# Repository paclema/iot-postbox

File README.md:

# IoT-PostBox

IoT-PostBox is a complete smart mailbox sensor solution that monitors mailbox activity and sends wireless notifications when events occur. The project consists of custom hardware designs with integrated battery management and charging system, and firmware that monitors switch sensors to detect mailbox events. The hardware has evolved from initial ESP8266-based designs (IoT-PostBox v0.x) to current ESP32S2-based designs (IoT-PostBox v1.x) with added LoRaWAN capabilities for extended range communication beyond WiFi and a optimized power management system. The device is designed for battery-powered operation with onboard charging circuitry. When an event is detected, the device wakes from deep sleep, connects wirelessly (WiFi or LoRa), publishes the event via MQTT or LoRaWAN, and returns to sleep to maximize battery life. The system includes device configuration and management through the WebConfigServer library, which provides a web-based dashboard to visualize data and handle device configurations easily using a config.json file.

**Installation and use:** The device is installed inside the mailbox with switches positioned to detect when the mail slot or door is opened. One switch can detect mail insertion (when the slot is opened to insert mail), while another can detect mail collection (when the mailbox door is opened to retrieve mail). This allows monitoring both mail delivery and pickup events.

**Hardware evolution:**
- **v0.x (ESP8266):** WiFi-only communication, basic power management using CH_PD pin to disable the microcontroller, battery charging system, switch sensor inputs.
- **v1.x (ESP32-S2):** Enhanced with LoRaWAN capability, improved power management with deep sleep modes managed by interrupts (allowing identification of wake-up source via WAKE_UP_BITMASK), advanced battery management, native USB programming, and expanded I/O options.

> [!NOTE]  
> For detailed hardware specifications, BOMs, and pinouts, see [`pcb_desings/readme.md`](pcb_desings/).

---

## 📁 Repository Structure

- `/src/` — Main firmware source code for IoT-PostBox
- `/pcb_desings/` — Hardware designs, documentation, BOMs, gerbers, and 3D models
- `/data/` — SPIFFS filesystem data (configs, static webapp, certificates)
- `/platformio.ini` — PlatformIO project configuration

---

## ⚡ Getting Started

1. **Select and configure your hardware:** 
   - **For IoT-PostBox PCBs:** Choose between IoT-PostBox v0.x (ESP8266-based) or IoT-PostBox v1.x (ESP32-S2-based) versions. See [`pcb_desings/readme.md`](pcb_desings/readme.md) for detailed specifications.
   - **For development boards:** The firmware also supports various ESP8266/ESP32 development boards (see available targets in `platformio.ini`), but full compatibility and functionality is only guaranteed with the custom IoT-PostBox PCBs designed for this purpose.
   - Configure the appropriate target in `platformio.ini` for your hardware version (e.g., `IoT-PostBox_v1` for IoT-PostBox v1.x PCB).
   - Edit `data/config/config.json` with your initial configuration (WiFi credentials, MQTT settings, etc.) following the WebConfigServer library standard.

2. **Upload SPIFFS data:**
   ```sh
   pio run -t uploadfs
   ```

3. **Build and upload firmware:** Use PlatformIO to compile and flash the firmware to your device.

4. **Configure the device:** Access the web dashboard hosted by the device for WiFi, MQTT, and power management setup, or update the configuration by editing `config.json` and re-uploading SPIFFS data.

---

## 📈 Web Dashboard

The static web dashboard is provided by the [WebConfigServer](https://github.com/paclema/WebConfigServer) library and served directly from the device.

If you need to customize the dashboard:
- Go to the WebConfigServer repository and follow the build instructions
- Copy the generated static files to the `/data/` folder
- Upload `/data/` to the device SPIFFS

---

## 📚 Dependencies

This project uses the following main libraries:
- [WebConfigServer](https://github.com/paclema/WebConfigServer) - Web dashboard and device configuration management
- [PowerManagement](https://github.com/paclema/PowerManagement) - Battery monitoring and power management

---

## 📄 License

[![CC BY-NC-SA 4.0][cc-by-nc-sa-image]][cc-by-nc-sa]&nbsp;&nbsp;&nbsp;<a property="dct:title" rel="cc:attributionURL" href="https://github.com/paclema/iot-postbox"> IoT-PostBox</a> © 2019-2025 by <a rel="cc:attributionURL dct:creator" property="cc:attributionName" href="http://www.paclema.com/">paclema</a> is licensed under <a href="http://creativecommons.org/licenses/by-nc-sa/4.0/?ref=chooser-v1" target="_blank" rel="license noopener noreferrer" style="display:inline-block;">CC BY-NC-SA 4.0</a>

**Hardware and firmware designs** are provided for educational and non-commercial use. For commercial use, please contact the author for permission.

[cc-by-nc-sa]: http://creativecommons.org/licenses/by-nc-sa/4.0/
[cc-by-nc-sa-image]: https://licensebuttons.net/l/by-nc-sa/4.0/88x31.png

---

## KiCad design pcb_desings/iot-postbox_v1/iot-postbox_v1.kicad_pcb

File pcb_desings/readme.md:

# IoT-PostBox PCB Designs

This folder contains all hardware designs for the IoT-PostBox project. These PCBs are intended for ultra-low power event detection and wireless notification, ideal for smart mailboxes or similar battery-powered IoT applications. The boards are designed to maximize battery life by staying in deep sleep and only waking up when an event is detected.  
**Typical use case:** Mount a switch at the mailbox slot or door to detect when a letter or package is inserted, triggering a wireless notification.

---

## 📝 How It Works

- **Event Detection:** The boards monitor switches (J1/J2) for events such as mailbox opening or mail insertion.
- **Wake-Up:** ESP8266 boards power on from switches, ESP32-S2 boards wake from deep sleep via GPIO interrupts
- **Notification:** Events are sent wirelessly (WiFi/MQTT for ESP8266, WiFi/MQTT and LoRaWAN for ESP32-S2)
- **Power Management:** Battery charging and monitoring circuits ensure safe operation and long battery life.

---

## 📦 IoT-Postbox v0.X (ESP8266/ESP-12)

- **Folder:** [`iot-postbox/`](iot-postbox/)
- **MCU:** ESP8266 (ESP-12F or ESP-07S)
- **Wake-up:** When either switch input (J1 or J2) closes, it physically pulls the CH_PD pin high, powering on the ESP8266 from a completely powered-down state. Once powered on, the firmware immediately activates GPIO14 to maintain CH_PD high, ensuring the system stays powered even if the switch opens during the notification process. After completing the notification and a configured delay, GPIO14 goes low, completely powering down the ESP8266 for maximum battery savings. The board can also be configured for deep sleep mode or continuous operation instead of complete power down via the onboard web app.
- **Features:**
  - Battery charger (TP4056) with overcharge, overdischarge, and overcurrent protection
  - Power management with LDO (candidates: ME6211 or MCP1700)
  - Switch sensor inputs for mailbox event detection
  - Deep sleep and wake-up logic via GPIO
  - WiFi and MQTT notifications for remote monitoring
- **Versions:**
  | v0.0 | v0.3 |
  |:----:|:----:|
  |  |  |
  | *First version* <br> Basic mailbox sensor with battery charger and power management. | *Added WS2812B LED strip for notifications* <br> *Updated battery sense resistors for improved ADC accuracy* <br> *Changed switch pinouts for better integration* |

- **Programming & Debugging:**  
  For ESP8266-based boards, external programming is required. Two options available:
  
  **Option 1: TTL-to-USB Adapter + FTDI Breakout**
  | Top View | Bottom View |
  |:------------------:|:----------------:|
  |  |  |
  - **Repository:** [`ttl_to_usb_adapter/`](ttl_to_usb_adapter/)
  - Converts DTR/RTS signals from an USB to Serial FTDI breakout board to ESP8266 boot sequence
  - Dedicated jumper for CH_PD control during programming

  **Option 2: Integrated USB Bridge**
  - **USBtoUART:** Complete solution available at [paclema.com/projects/usbtouart/](https://paclema.com/projects/usbtouart/) or at github.com/paclema/USBtoUART
  - Single device with integrated USB-to-UART conversion

---

## 📦 IoT-Postbox v1 (ESP32-S2)

- **Folder:** [`iot-postbox_v1/`](iot-postbox_v1/)
- **MCU:** ESP32-S2
- **Wake-up:** Switches (J1/J2) are configured as GPIO interrupts to wake up the MCU from deep sleep, instead of physically powering on the board (as in ESP8266). This allows more flexible event handling and enables distinguishing between different events.
- **Features:**
  - LoRa support (RFM95W module footprints)
  - Up to 16MB flash and 8MB PSRAM (optional, depending on SoC version)
  - Improved battery and power management (dedicated ADC sense for VBAT and VBUS)
  - Modular schematic split into INTERFACE, MCU, and POWER sections
  - Selectable onboard/uFL antennas for WiFi (JP1) and LoRa (JP2) by populating the correct resistor
  - Dedicated JTAG debug port
  - Multiple jumpers and test points on the back for configuration and debugging (including RPROG selection for battery charger IC)

- **Latest version:** IoT-PostBox v1.2
  | Top View | Bottom View |
  |:--------------:|:----------------:|
  |  |  |

- **Programming & Debugging:**  
  Programming and debugging for the ESP32-S2 board does **not require an external USB-to-UART bridge**. The ESP32-S2 features a native USB interface (USB-CDC/JTAG), allowing direct programming and serial communication via the onboard USB connector. Simply connect the board to your computer using a USB cable for firmware flashing and debugging.

### LiPo Charger & RPROG Selection

The onboard charger circuit is designed to be compatible with MCP73831/2, TP4054, and TP4065 ICs, allowing any of these to be used. The charging current is set by the RPROG resistor.

- **For MCP73831/2 (max 500mA) and TP4054 (max 800mA):**
  ```
  Ichg (mA) = 1000(v) / R(kΩ)
  ```
  | RPROG (Ω) | Charging Current (mA) |
  |-----------|----------------------|
  | 10k       | 100                  |
  | 5k        | 200                  |
  | 2k2       | 455                  |
  | 2k        | 500                  |
  | 1k        | 1000                 |

- **For TP4065 (max 600mA):**
  ```
  Ichg (mA) = 1100(v) / R(kΩ)
  ```
  | RPROG (Ω) | Charging Current (mA) |
  |-----------|----------------------|
  | 2k2       | 500                  |
  | 2k        | 600                  |

- **Note:**  
  - Choose the RPROG value based on your battery's specifications and desired charging speed.
  - Protections: Battery and input reverse polarity protection but no temperature or overcurrent protection.

- **VBAT_STAT output:**  
  - Tri-state output: for MCP73831.
  - Open-drain output: for MCP7383, TP4054 and TP4065.
  - Only for open-drain, `R18` makes sense because VDD_STAT can be configurable only in that case.
  - Monitored using ESP32-S2 GPIO3/ADC1_CH2 pin.

### Pinout Reference (IoT-Postbox v1.2)

Below are the pinouts for the main connectors on the back of the IoT-Postbox v1.2 PCB, including signal and ESP32-S2 functions:

#### J6 (EXT1 Expansion Port):

| Pin | Signal   | Function                                            |
|-----|----------|--------------------------------------------------------|
| 1   | GPIO46   | Strapping pin (can be used for boot mode selection)    |
| 2   | GPIO45   | Strapping pin (can be used for VDD_SPI selection)      |
| 3   | GPIO44   | UART0 RXD (default)                                    |
| 4   | GPIO43   | UART0 TXD (default)                                    |
| 5   | GPIO38   | I2C SCL (default)                                      |
| 6   | GPIO37   | SPI MISO (default)                                     |

#### J3 (LED Port):

| Pin | Signal      | Function                                 |
|-----|-------------|---------------------------------------------|
| 1   | VCC         | Power for LED strip (3V3_LDO2)              |
| 2   | RGB_LED_PWM | PWM output for RGB LED strip                |
| 3   | GND         | Ground                                      |

#### J5 (Power Output Port):

| Pin | Signal   | Function                                   |
|-----|----------|-----------------------------------------------|
| 1   | 3V3_LDO2 | Power output from peripheral LDO              |
| 2   | GND      | Ground                                        |

#### SW1 (Switch Sensor 1):

| Pin | Signal   | Function                                   |
|-----|----------|-----------------------------------------------|
| 1   | 3V3_LDO  | Power for switch sensor                       |
| 2   | SW1      | Digital input (event detection, GPIO input)   |

#### SW2 (Switch Sensor 2):

| Pin | Signal   | Function                                   |
|-----|----------|-----------------------------------------------|
| 1   | 3V3_LDO  | Power for switch sensor                       |
| 2   | SW2      | Digital input (event detection, GPIO input)   |

#### J7 (EXT2 Expansion Port):

| Pin | Signal   | Function                                   |
|-----|----------|-----------------------------------------------|
| 1   | CHIP_PU  | ESP32-S2 enable (power up, active high)       |
| 2   | BOOT     | Boot mode selection (GPIO0, strapping pin)    |
| 3   | GPIO34   | SPI MOSI (default)                            |
| 4   | GPIO35   | SPI SCK (default)                             |
| 5   | GPIO36   | SPI CS (default)                              |
| 6   | GPIO33   | I2C SDA (default)                             |

---

### 📚 Libraries

- **Folder:** [`libs/`](libs/)
- Contains KiCad symbols, footprints and 3D models, including Espressif official libraries and miscellaneous modules.

---

### 🛠️ Submodules Installation for KiCad

To pull KiCad lib submodules, run:
```sh
git submodule update --init --recursive
```

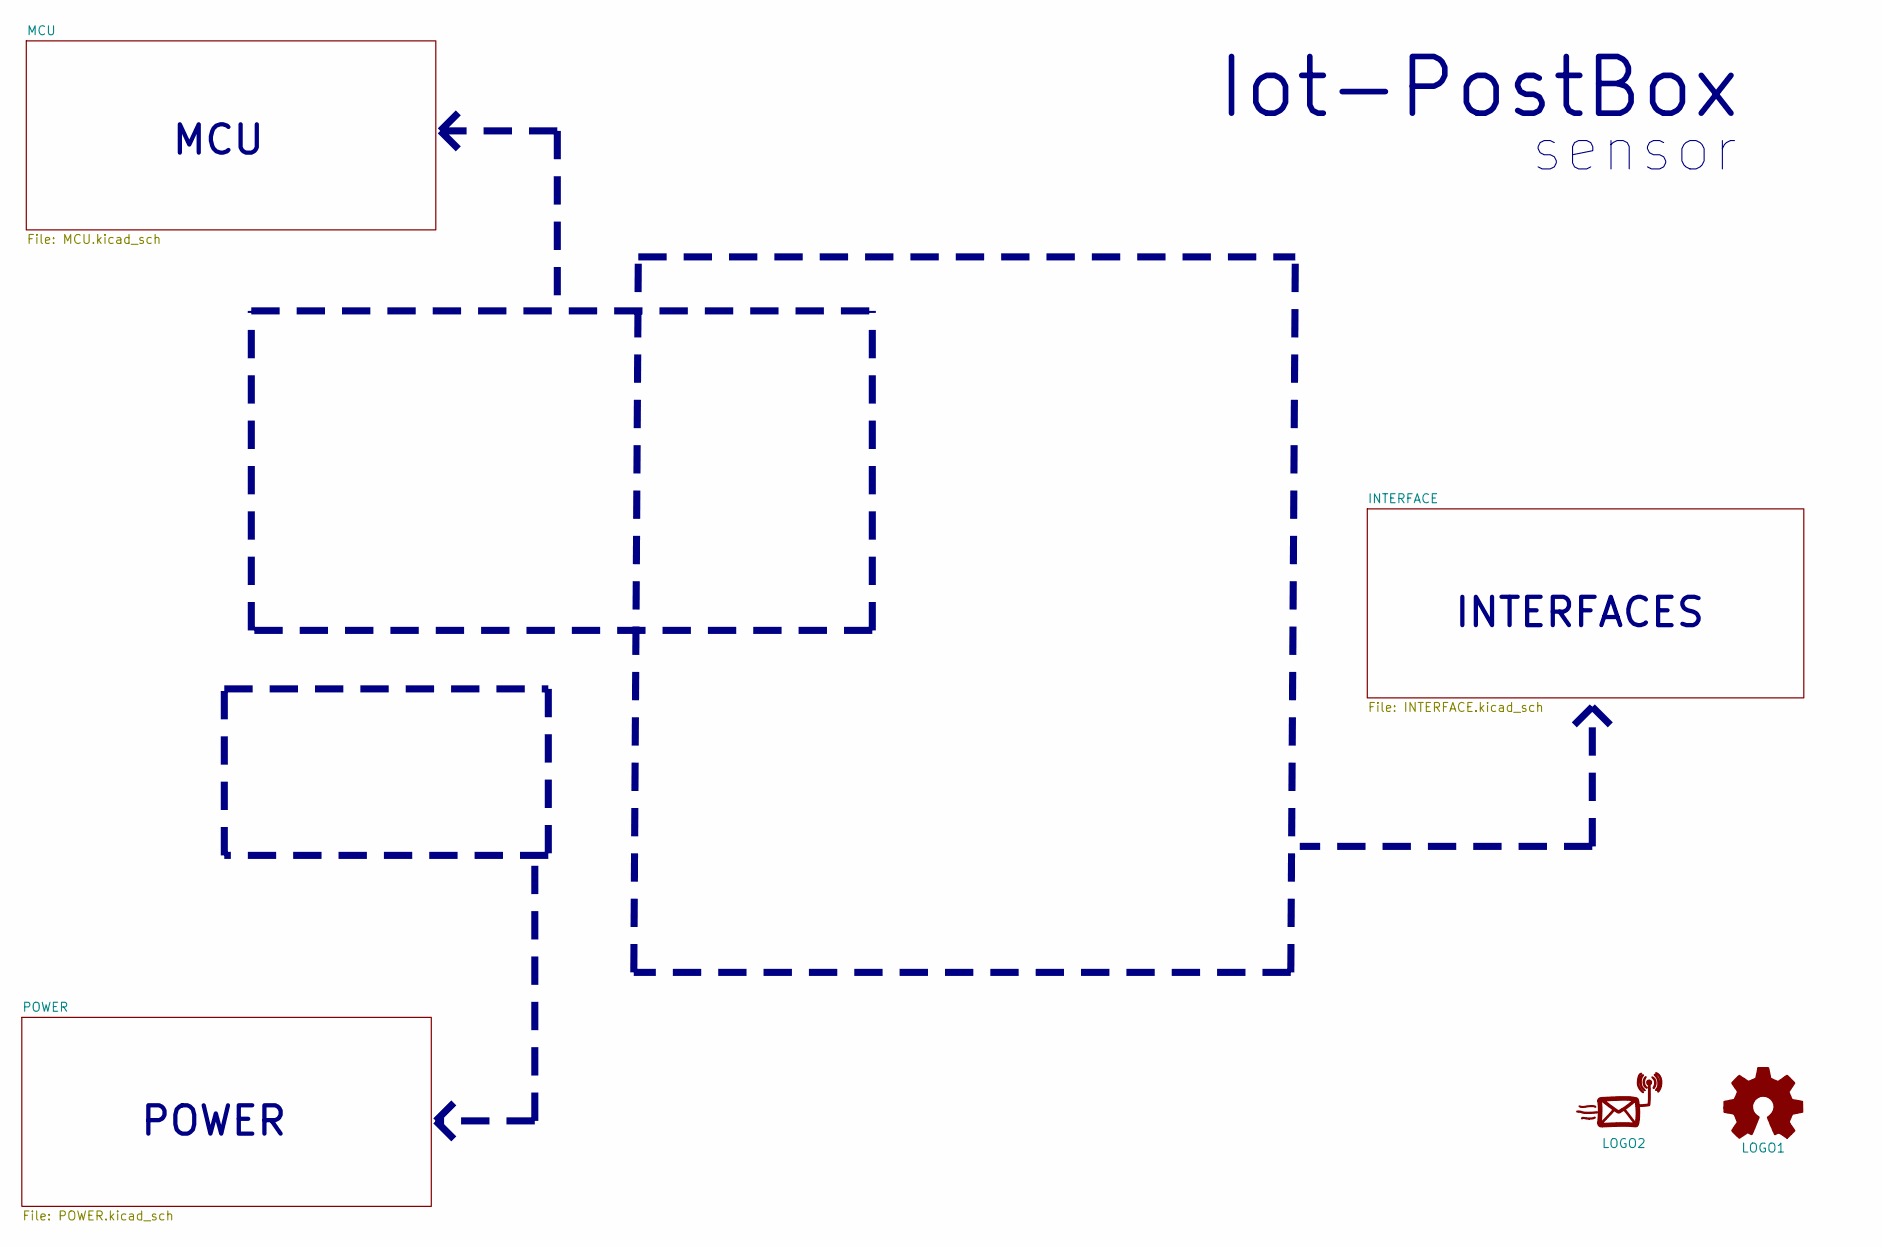
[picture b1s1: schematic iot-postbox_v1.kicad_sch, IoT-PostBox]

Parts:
LOGO1: Logo_Open_Hardware_Small; OSHW-Logo_5.7x6mm_SilkScreen
LOGO2: iot-postbox_logo

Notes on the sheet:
Iot-PostBox
POWER
INTERFACES
MCU
sensor

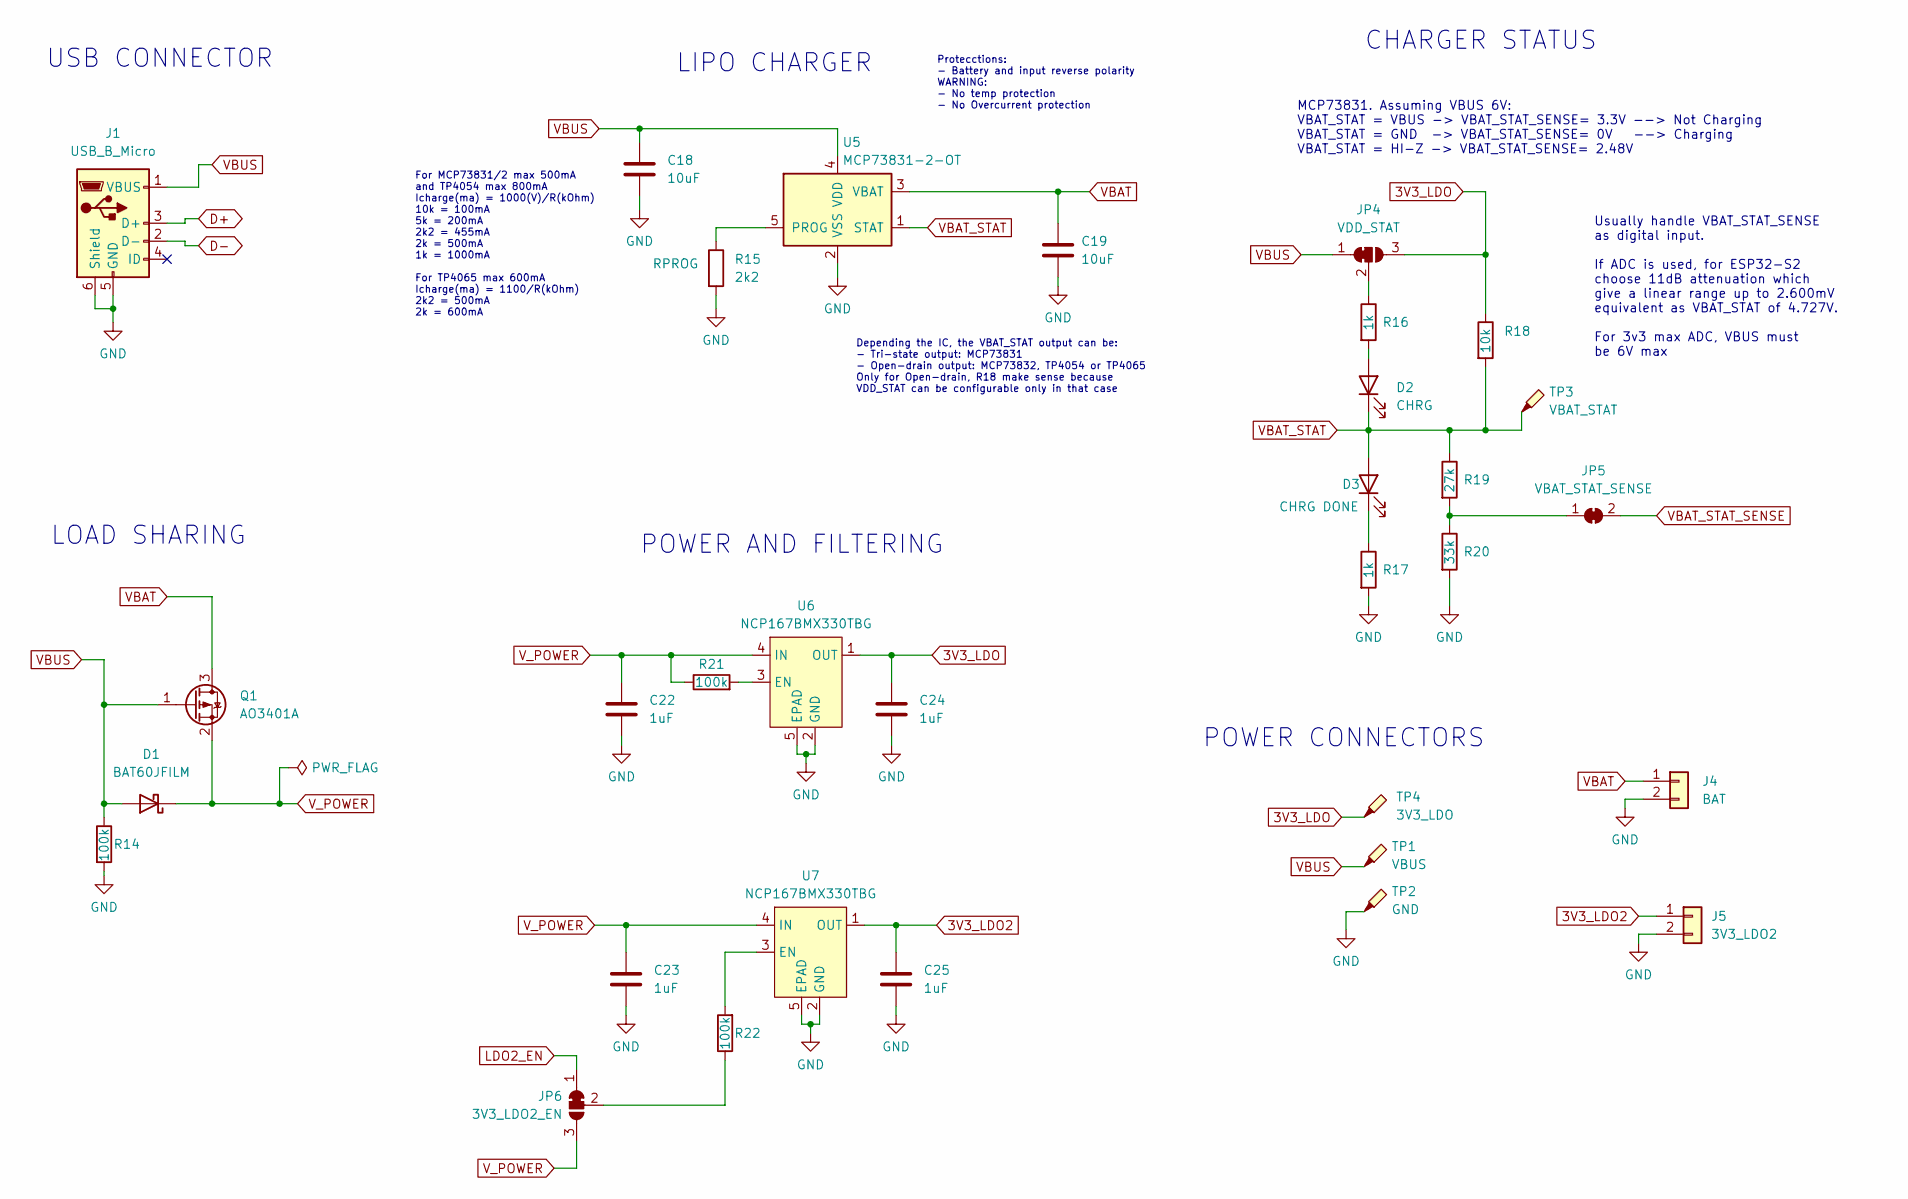
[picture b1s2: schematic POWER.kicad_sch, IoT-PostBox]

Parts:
C18, C19: 10uF; C_1206_3216Metric; Mouser CL31A106KAHNNNF
C22, C23, C24, C25: 1uF; C_0603_1608Metric; Mouser CL10A105KA8NNNC
D1: BAT60JFILM; D_SOD-323; LCSC C133103
D2: CHRG; LED_0805_2012Metric
D3: CHRG DONE; LED_0805_2012Metric
J1: USB_B_Micro; USB_Micro-B_Amphenol_10118194_Horizontal
J4: BAT; PinHeader_1x02_P2.54mm_Vertical
J5: 3V3_LDO2; PinHeader_1x02_P2.54mm_Vertical
JP4: VDD_STAT; SolderJumper-3_P1.3mm_Bridged12_RoundedPad1.0x1.5mm_NumberL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
JP5: VBAT_STAT_SENSE; SolderJumper-2_P1.3mm_Bridged_RoundedPad1.0x1.5mm
JP6: 3V3_LDO2_EN; SolderJumper-3_P1.3mm_Bridged12_RoundedPad1.0x1.5mm_NumberL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
Q1: AO3401A; SOT-23; LCSC C2836398
R14: 100k; R_0805_2012Metric; Mouser RC0805FR-07100KL
R15: 2k2; R_0805_2012Metric; Mouser CR0805-JW-222ELF
R16, R17: 1k; R_0805_2012Metric; Mouser AC0805FR-071KL
R18: 10k; R_0805_2012Metric; Mouser AC0805JR-0710KL
R19: 27k; R_0805_2012Metric; Mouser RC0805FR-1327KL
R20: 33k; R_0805_2012Metric; Mouser RC0805FR-0733KL
R21, R22: 100k; R_0603_1608Metric; Mouser RK73B1JTTD104J
TP1: VBUS; TestPoint_Pad_D2.5mm
TP2: GND; TestPoint_Pad_D2.5mm
TP3: VBAT_STAT; TestPoint_Pad_D2.0mm
TP4: 3V3_LDO; TestPoint_Pad_D2.0mm
U5: MCP73831-2-OT; SOT-23-5; Mouser MCP73831T-2ACI/OT
U6, U7: NCP167BMX330TBG; NCP167BMX330TBG_XDFN4; Mouser NCP167BMX330TBG

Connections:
3V3_LDO: C24.1, JP4.3 (B), R18.1, TP4.1, U6.1 (OUT); also elsewhere on the board
3V3_LDO2: C25.1, J5.1, U7.1 (OUT); also elsewhere on the board
D+: J1.3 (D+); also elsewhere on the board
D-: J1.2 (D-); also elsewhere on the board
GND: C18.2, C19.2, C22.2, C23.2, C24.2, C25.2, J1.5 (GND), J1.6 (Shield), J4.2, J5.2, R14.2, R15.2, R17.2, R20.2, TP2.1, U5.2 (VSS), U6.2 (GND), U6.5 (EPAD), U7.2 (GND), U7.5 (EPAD); also elsewhere on the board
LDO2_EN: JP6.1 (A); also elsewhere on the board
unnamed: D2.2 (A), R16.2
unnamed: D3.1 (K), R17.1
unnamed: JP4.2 (C), R16.1
unnamed: JP5.1 (A), R19.2, R20.1
unnamed: JP6.2 (C), R22.1
unnamed: R15.1, U5.5 (PROG)
unnamed: R21.2, U6.3 (EN)
unnamed: R22.2, U7.3 (EN)
VBAT: C19.1, J4.1, Q1.3 (D), U5.3 (VBAT); also elsewhere on the board
VBAT_STAT: D2.1 (K), D3.2 (A), R18.2, R19.1, TP3.1, U5.1 (STAT)
VBAT_STAT_SENSE: JP5.2 (B); also elsewhere on the board
VBUS: C18.1, D1.2 (A), J1.1 (VBUS), JP4.1 (A), Q1.1 (G), R14.1, TP1.1, U5.4 (VDD); also elsewhere on the board
V_POWER: C22.1, C23.1, D1.1 (K), JP6.3 (B), Q1.2 (S), R21.1, U6.4 (IN), U7.4 (IN); also elsewhere on the board

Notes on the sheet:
LOAD SHARING
POWER CONNECTORS
Usually handle VBAT_STAT_SENSE as digital input. If ADC is used, for ESP32-S2 choose 11dB attenuation which give a linear range up to 2.600mV equivalent as VBAT_STAT of 4.727V. For 3v3 max ADC, VBUS must be 6V max
For MCP73831/2 max 500mA and TP4054 max 800mA Icharge(ma) = 1000(V)/R(kOhm) 10k = 100mA 5k = 200mA 2k2 = 455mA 2k = 500mA 1k = 1000mA For TP4065 max 600mA Icharge(ma) = 1100/R(kOhm) 2k2 = 500mA 2k = 600mA
POWER AND FILTERING
CHARGER STATUS
Depending the IC, the VBAT_STAT output can be: - Tri-state output: MCP73831 - Open-drain output: MCP73832, TP4054 or TP4065 Only for Open-drain, R18 make sense because VDD_STAT can be configurable only in that case
LIPO CHARGER
Protecctions: - Battery and input reverse polarity WARNING: - No temp protection - No Overcurrent protection
MCP73831. Assuming VBUS 6V: VBAT_STAT = VBUS -> VBAT_STAT_SENSE= 3.3V --> Not Charging VBAT_STAT = GND -> VBAT_STAT_SENSE= 0V --> Charging VBAT_STAT = HI-Z -> VBAT_STAT_SENSE= 2.48V
USB CONNECTOR

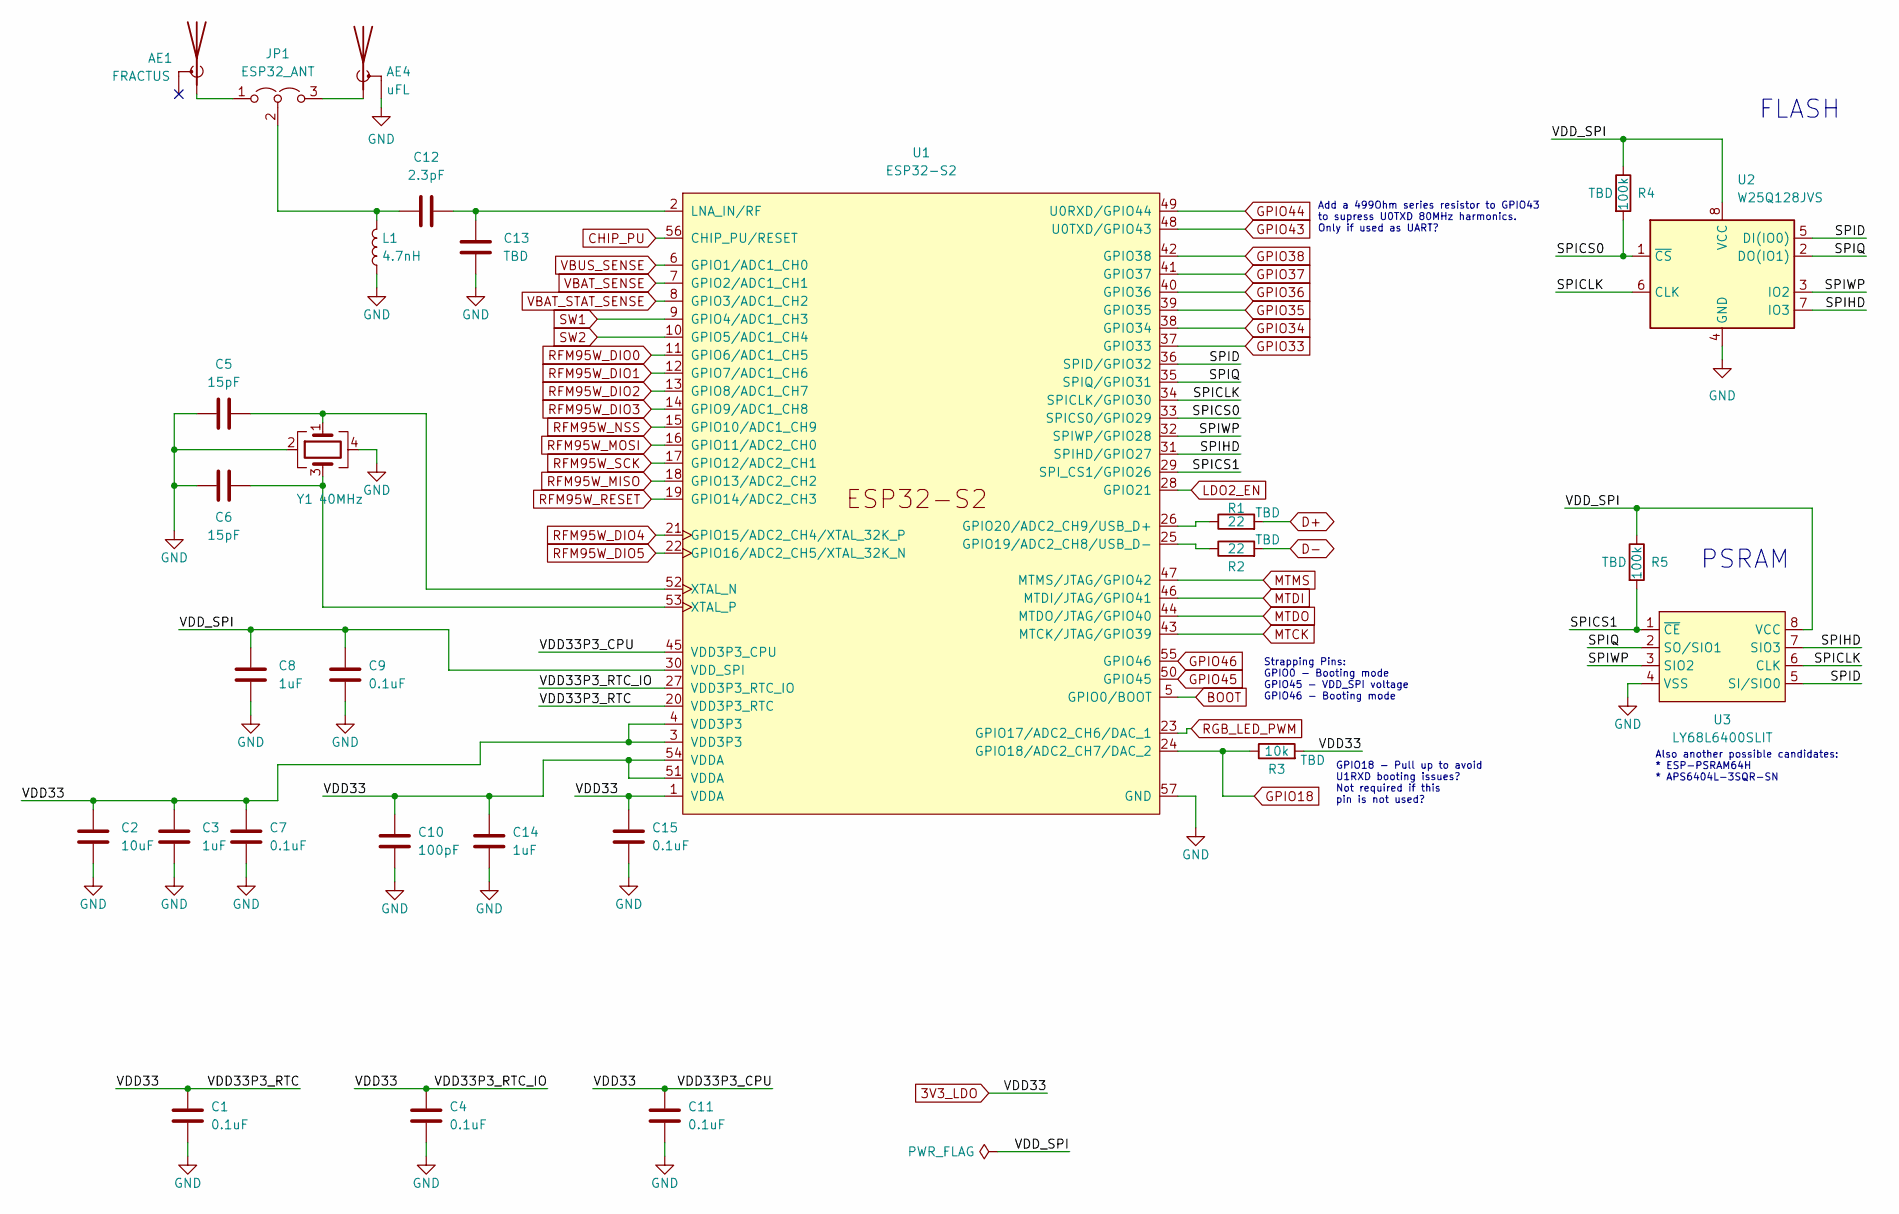
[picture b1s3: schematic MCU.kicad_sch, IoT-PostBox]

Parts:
AE1: FRACTUS; NN01-102; Mouser NN01-102
AE4: uFL; U.FL_Molex_MCRF_73412-0110_Vertical; Mouser RECE.20279.001E.01
C1, C4, C7, C9, C11, C15: 0.1uF; C_0603_1608Metric; Mouser CL10B104KB8NNWC
C2: 10uF; C_1206_3216Metric; Mouser CL31A106KAHNNNF
C3, C8, C14: 1uF; C_0805_2012Metric; Mouser EMK212BJ105KG-T
C5, C6: 15pF; C_0603_1608Metric; Mouser 06035A150JAT2A
C10: 100pF; C_0603_1608Metric; Mouser GRM1885C1H101JA01D
C12: 2.3pF; C_0402_1005Metric; Mouser GRM1555C2A2R3CA01J
C13: TBD; C_0402_1005Metric; Mouser AC0402JR-130RL
JP1: ESP32_ANT; Jumper_0402_x3; Mouser AC0402JR-130RL
L1: 4.7nH; L_0402_1005Metric; Mouser LCCI0402S4N7GTAR or shielded 7447840047G
R1, R2: 22; R_0603_1608Metric; Mouser RC0603FR-1022RL
R3: 10k; R_0603_1608Metric; Mouser RC0603JR-0710KL
R4, R5: 100k; R_0603_1608Metric; Mouser RK73B1JTTD104J
U1: ESP32-S2; ESP32_S2_QFN56; Mouser ESP32-S2
U2: W25Q128JVS; SOIC-8_5.23x5.23mm_P1.27mm; Mouser W25Q128JVSIM TR
U3: LY68L6400SLIT; SOP-8_3.9x4.9mm_P1.27mm; LCSC C261881
Y1: 40MHz; ECS-400-10-37B2-CKM-TR; Mouser ECS-400-10-37B2-CKM

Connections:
3V3_LDO: C1.1, C2.1, C3.1, C4.1, C7.1, C10.1, C11.1, C14.1, C15.1, R3.2, U1.1 (VDDA), U1.3 (VDD3P3), U1.4 (VDD3P3), U1.20 (VDD3P3_RTC), U1.27 (VDD3P3_RTC_IO), U1.45 (VDD3P3_CPU), U1.51 (VDDA), U1.54 (VDDA); also elsewhere on the board
/MCU/SPICLK: U1.34 (SPICLK/GPIO30), U2.6 (CLK), U3.6 (CLK)
/MCU/SPICS0: R4.2, U1.33 (SPICS0/GPIO29), U2.1 (~CS)
/MCU/SPICS1: R5.2, U1.29 (SPI_CS1/GPIO26), U3.1 (~CE)
/MCU/SPID: U1.36 (SPID/GPIO32), U2.5 (DI(IO0)), U3.5 (SI/SIO0)
/MCU/SPIHD: U1.31 (SPIHD/GPIO27), U2.7 (IO3), U3.7 (SIO3)
/MCU/SPIQ: U1.35 (SPIQ/GPIO31), U2.2 (DO(IO1)), U3.2 (SO/SIO1)
/MCU/SPIWP: U1.32 (SPIWP/GPIO28), U2.3 (IO2), U3.3 (SIO2)
/MCU/VDD_SPI: C8.1, C9.1, R4.1, R5.1, U1.30 (VDD_SPI), U2.8 (VCC), U3.8 (VCC)
BOOT: U1.5 (GPIO0/BOOT); also elsewhere on the board
CHIP_PU: U1.56 (CHIP_PU/RESET); also elsewhere on the board
D+: R1.2; also elsewhere on the board
D-: R2.2; also elsewhere on the board
GND: AE4.2 (Shield), C1.2, C2.2, C3.2, C4.2, C5.1, C6.1, C7.2, C8.2, C9.2, C10.2, C11.2, C13.2, C14.2, C15.2, L1.1, U1.57 (GND), U2.4 (GND), U3.4 (VSS), Y1.2, Y1.4; also elsewhere on the board
GPIO18: R3.1, U1.24 (GPIO18/ADC2_CH7/DAC_2)
GPIO33: U1.37 (GPIO33); also elsewhere on the board
GPIO34: U1.38 (GPIO34); also elsewhere on the board
GPIO35: U1.39 (GPIO35); also elsewhere on the board
GPIO36: U1.40 (GPIO36); also elsewhere on the board
GPIO37: U1.41 (GPIO37); also elsewhere on the board
GPIO38: U1.42 (GPIO38); also elsewhere on the board
GPIO43: U1.48 (U0TXD/GPIO43); also elsewhere on the board
GPIO44: U1.49 (U0RXD/GPIO44); also elsewhere on the board
GPIO45: U1.50 (GPIO45); also elsewhere on the board
GPIO46: U1.55 (GPIO46); also elsewhere on the board
LDO2_EN: U1.28 (GPIO21); also elsewhere on the board
MTCK: U1.43 (MTCK/JTAG/GPIO39); also elsewhere on the board
MTDI: U1.46 (MTDI/JTAG/GPIO41); also elsewhere on the board
MTDO: U1.44 (MTDO/JTAG/GPIO40); also elsewhere on the board
MTMS: U1.47 (MTMS/JTAG/GPIO42); also elsewhere on the board
unnamed: AE1.1 (A), JP1.1 (A)
unnamed: AE4.1 (A), JP1.3 (B)
unnamed: C12.1, JP1.2 (C), L1.2
unnamed: R2.1, U1.25 (GPIO19/ADC2_CH8/USB_D-)
unnamed: R1.1, U1.26 (GPIO20/ADC2_CH9/USB_D+)
unnamed: C12.2, C13.1, U1.2 (LNA_IN/RF)
unnamed: C5.2, U1.52 (XTAL_N), Y1.1
unnamed: C6.2, U1.53 (XTAL_P), Y1.3
RFM95W_DIO0: U1.11 (GPIO6/ADC1_CH5); also elsewhere on the board
RFM95W_DIO1: U1.12 (GPIO7/ADC1_CH6); also elsewhere on the board
RFM95W_DIO2: U1.13 (GPIO8/ADC1_CH7); also elsewhere on the board
RFM95W_DIO3: U1.14 (GPIO9/ADC1_CH8); also elsewhere on the board
RFM95W_DIO4: U1.21 (GPIO15/ADC2_CH4/XTAL_32K_P); also elsewhere on the board
RFM95W_DIO5: U1.22 (GPIO16/ADC2_CH5/XTAL_32K_N); also elsewhere on the board
RFM95W_MISO: U1.18 (GPIO13/ADC2_CH2); also elsewhere on the board
RFM95W_MOSI: U1.16 (GPIO11/ADC2_CH0); also elsewhere on the board
RFM95W_NSS: U1.15 (GPIO10/ADC1_CH9); also elsewhere on the board
RFM95W_RESET: U1.19 (GPIO14/ADC2_CH3); also elsewhere on the board
RFM95W_SCK: U1.17 (GPIO12/ADC2_CH1); also elsewhere on the board
RGB_LED_PWM: U1.23 (GPIO17/ADC2_CH6/DAC_1); also elsewhere on the board
SW1: U1.9 (GPIO4/ADC1_CH3); also elsewhere on the board
SW2: U1.10 (GPIO5/ADC1_CH4); also elsewhere on the board
VBAT_SENSE: U1.7 (GPIO2/ADC1_CH1); also elsewhere on the board
VBAT_STAT_SENSE: U1.8 (GPIO3/ADC1_CH2); also elsewhere on the board
VBUS_SENSE: U1.6 (GPIO1/ADC1_CH0); also elsewhere on the board

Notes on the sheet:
Also another possible candidates: * ESP-PSRAM64H * APS6404L-3SQR-SN
PSRAM
Add a 499Ohm series resistor to GPIO43 to supress U0TXD 80MHz harmonics. Only if used as UART?
GPIO18 - Pull up to avoid U1RXD booting issues? Not required if this pin is not used?
Strapping Pins: GPIO0 - Booting mode GPIO45 - VDD_SPI voltage GPIO46 - Booting mode
FLASH

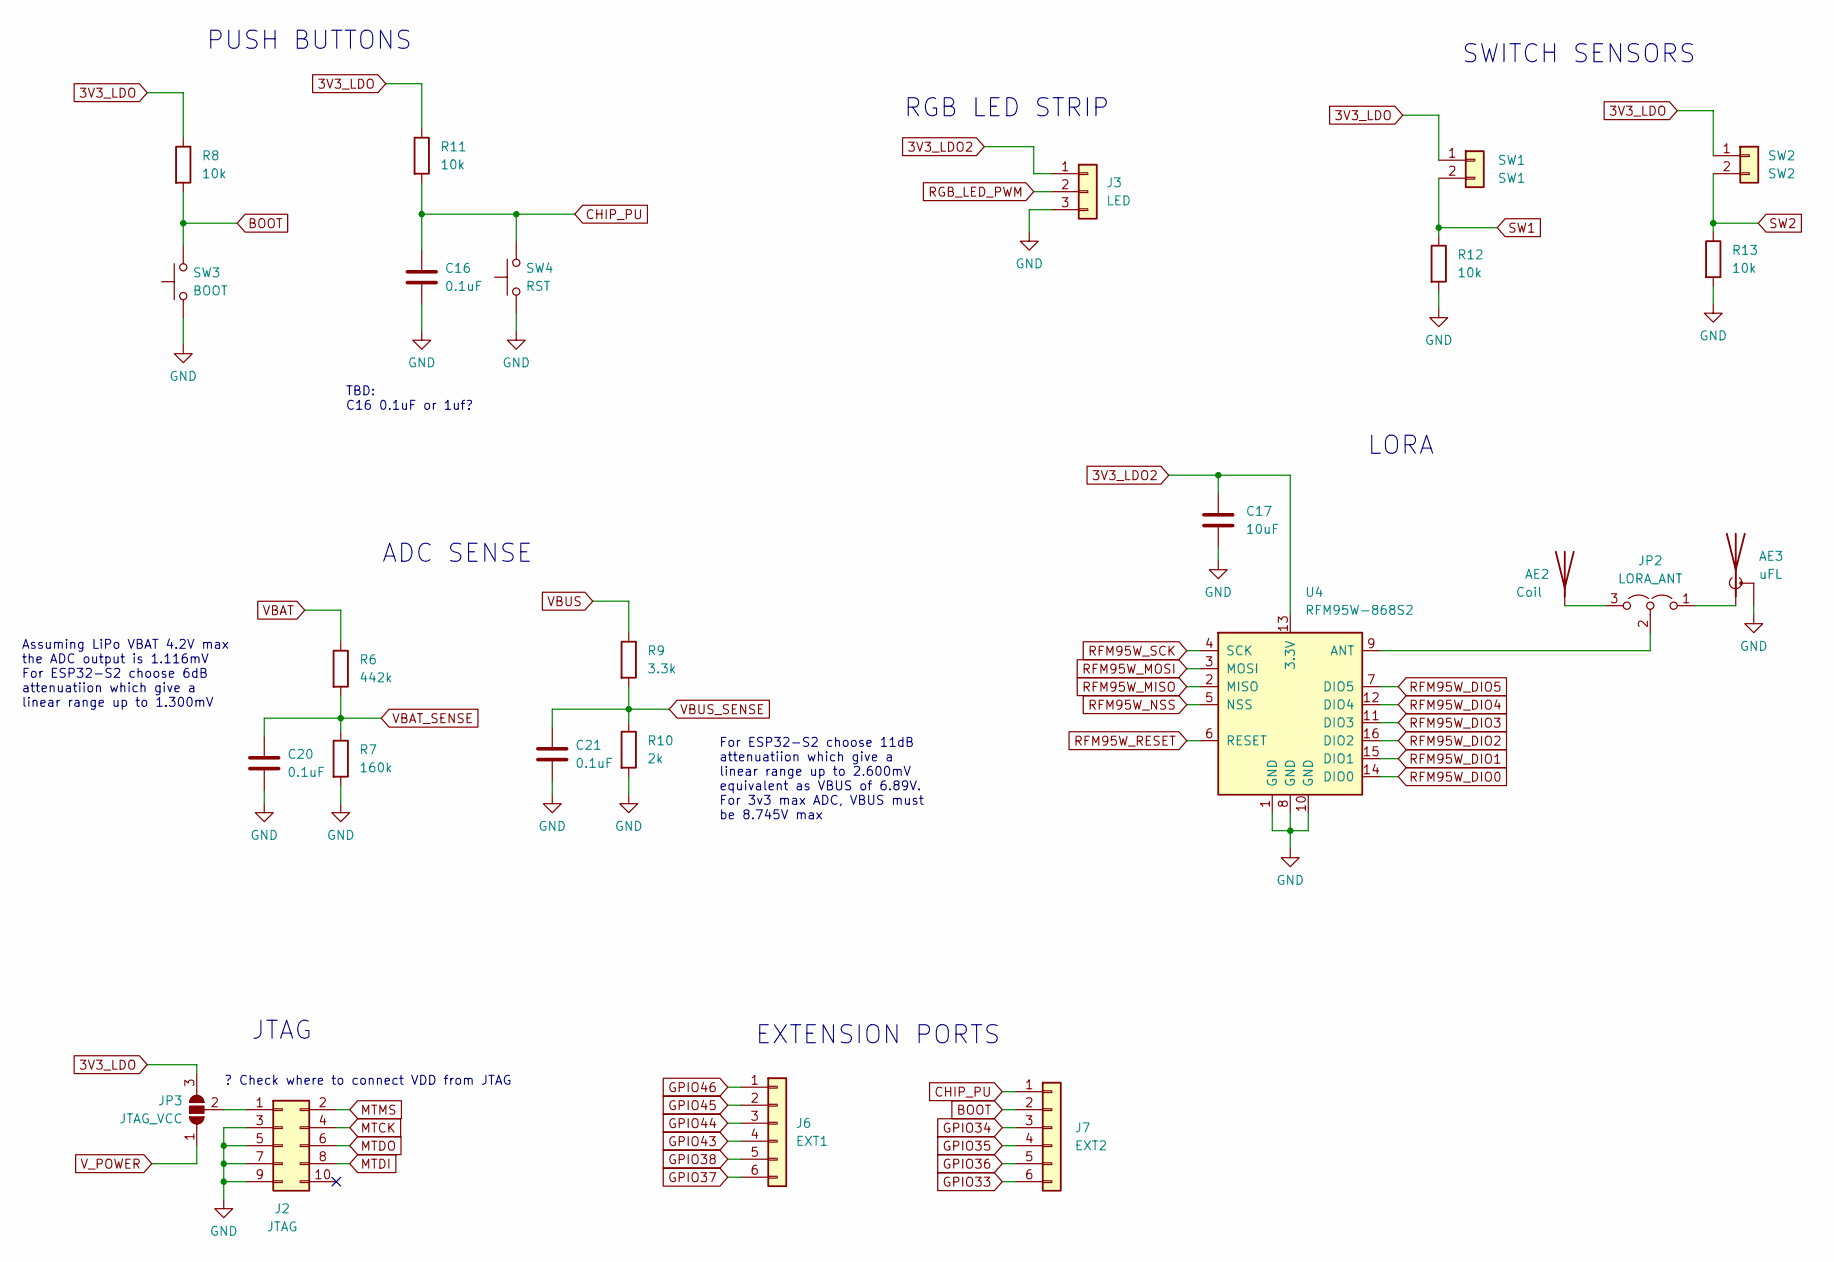
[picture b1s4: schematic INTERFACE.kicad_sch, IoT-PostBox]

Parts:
AE2: Coil; 868Mhz_sprin_antenna_SW868-TH13; LCSC T3-868M or VG868SNX18-5W2
AE3: uFL; U.FL_Molex_MCRF_73412-0110_Vertical; Mouser RECE.20279.001E.01
C16, C20, C21: 0.1uF; C_0603_1608Metric; Mouser CL10B104KB8NNWC
C17: 10uF; C_1206_3216Metric; Mouser CL31A106KAHNNNF
J2: JTAG; PinHeader_2x05_P2.54mm_Vertical_SMD; LCSC C124391
J3: LED; PinHeader_1x03_P2.54mm_Vertical
J6: EXT1; PinHeader_1x06_P2.54mm_Vertical
J7: EXT2; PinHeader_1x06_P2.54mm_Vertical
JP2: LORA_ANT; Jumper_0402_x3; Mouser AC0402JR-130RL
JP3: JTAG_VCC; SolderJumper-3_P2.0mm_Open_TrianglePad1.0x1.5mm_NumberLabels
R6: 442k; R_0805_2012Metric; Mouser RC0805FR-07442KL
R7: 160k; R_0805_2012Metric; Mouser CR0805-FX-1603ELF
R8, R11, R12, R13: 10k; R_0603_1608Metric; Mouser RC0603JR-0710KL
R9: 3.3k; R_0805_2012Metric; Mouser RC0805FR-133K3L
R10: 2k; R_0805_2012Metric; Mouser RT0805FRE072KL
SW1: SW1; PinHeader_1x02_P2.54mm_Vertical
SW2: SW2; PinHeader_1x02_P2.54mm_Vertical
SW3: BOOT; SW_Push_SPST_NO_Alps_SKRK; LCSC C843669
SW4: RST; SW_Push_SPST_NO_Alps_SKRK; LCSC C843669
U4: RFM95W-868S2; HOPERF_RFM9XW_SMD; LCSC C2844472

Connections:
3V3_LDO: JP3.3 (B), R8.1, R11.1, SW1.1, SW2.1; also elsewhere on the board
3V3_LDO2: C17.1, J3.1, U4.13 (3.3V); also elsewhere on the board
BOOT: J7.2, R8.2, SW3.2; also elsewhere on the board
CHIP_PU: C16.1, J7.1, R11.2, SW4.2; also elsewhere on the board
GND: AE3.2 (Shield), C16.2, C17.2, C20.2, C21.2, J2.3, J2.5, J2.7, J2.9, J3.3, R7.2, R10.2, R12.2, R13.2, SW3.1, SW4.1, U4.1 (GND), U4.8 (GND), U4.10 (GND); also elsewhere on the board
GPIO33: J7.6; also elsewhere on the board
GPIO34: J7.3; also elsewhere on the board
GPIO35: J7.4; also elsewhere on the board
GPIO36: J7.5; also elsewhere on the board
GPIO37: J6.6; also elsewhere on the board
GPIO38: J6.5; also elsewhere on the board
GPIO43: J6.4; also elsewhere on the board
GPIO44: J6.3; also elsewhere on the board
GPIO45: J6.2; also elsewhere on the board
GPIO46: J6.1; also elsewhere on the board
MTCK: J2.4; also elsewhere on the board
MTDI: J2.8; also elsewhere on the board
MTDO: J2.6; also elsewhere on the board
MTMS: J2.2; also elsewhere on the board
unnamed: AE2.1 (A), JP2.3 (B)
unnamed: AE3.1 (A), JP2.1 (A)
unnamed: J2.1, JP3.2 (C)
unnamed: JP2.2 (C), U4.9 (ANT)
RFM95W_DIO0: U4.14 (DIO0); also elsewhere on the board
RFM95W_DIO1: U4.15 (DIO1); also elsewhere on the board
RFM95W_DIO2: U4.16 (DIO2); also elsewhere on the board
RFM95W_DIO3: U4.11 (DIO3); also elsewhere on the board
RFM95W_DIO4: U4.12 (DIO4); also elsewhere on the board
RFM95W_DIO5: U4.7 (DIO5); also elsewhere on the board
RFM95W_MISO: U4.2 (MISO); also elsewhere on the board
RFM95W_MOSI: U4.3 (MOSI); also elsewhere on the board
RFM95W_NSS: U4.5 (NSS); also elsewhere on the board
RFM95W_RESET: U4.6 (RESET); also elsewhere on the board
RFM95W_SCK: U4.4 (SCK); also elsewhere on the board
RGB_LED_PWM: J3.2; also elsewhere on the board
SW1: R12.1, SW1.2; also elsewhere on the board
SW2: R13.1, SW2.2; also elsewhere on the board
VBAT: R6.1; also elsewhere on the board
VBAT_SENSE: C20.1, R6.2, R7.1; also elsewhere on the board
VBUS: R9.1; also elsewhere on the board
VBUS_SENSE: C21.1, R9.2, R10.1; also elsewhere on the board
V_POWER: JP3.1 (A); also elsewhere on the board

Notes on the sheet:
RGB LED STRIP
PUSH BUTTONS
TBD: C16 0.1uF or 1uf?
? Check where to connect VDD from JTAG
SWITCH SENSORS
Assuming LiPo VBAT 4.2V max the ADC output is 1.116mV For ESP32-S2 choose 6dB attenuatiion which give a linear range up to 1.300mV
LORA
For ESP32-S2 choose 11dB attenuatiion which give a linear range up to 2.600mV equivalent as VBUS of 6.89V. For 3v3 max ADC, VBUS must be 8.745V max
ADC SENSE
EXTENSION PORTS
JTAG

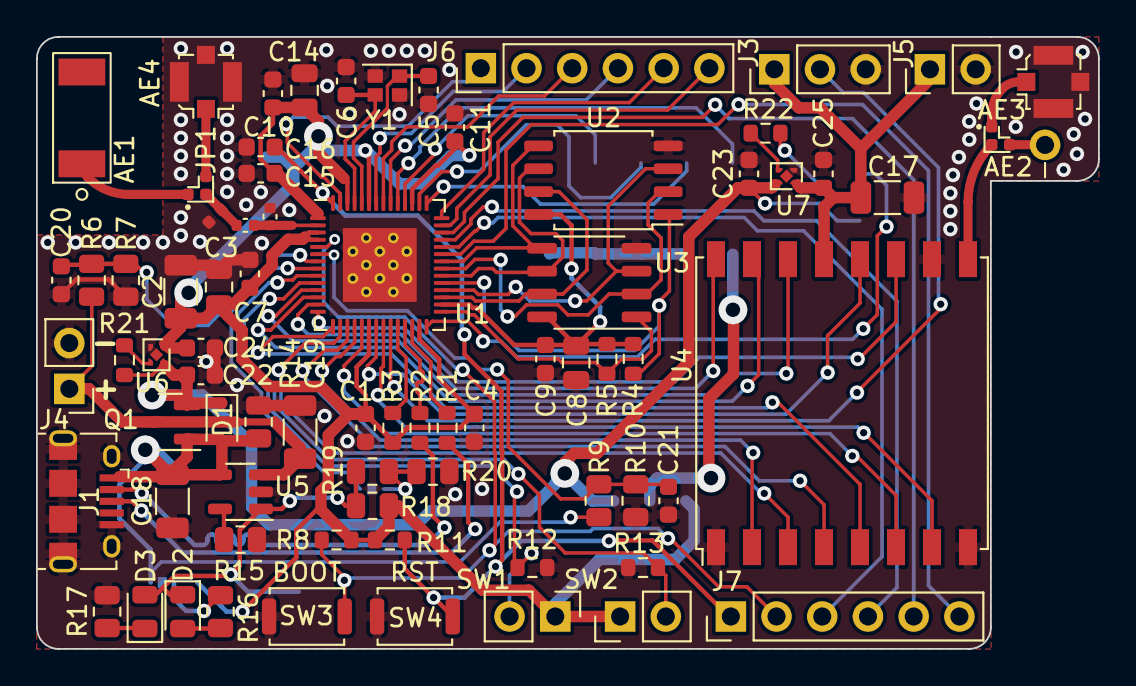
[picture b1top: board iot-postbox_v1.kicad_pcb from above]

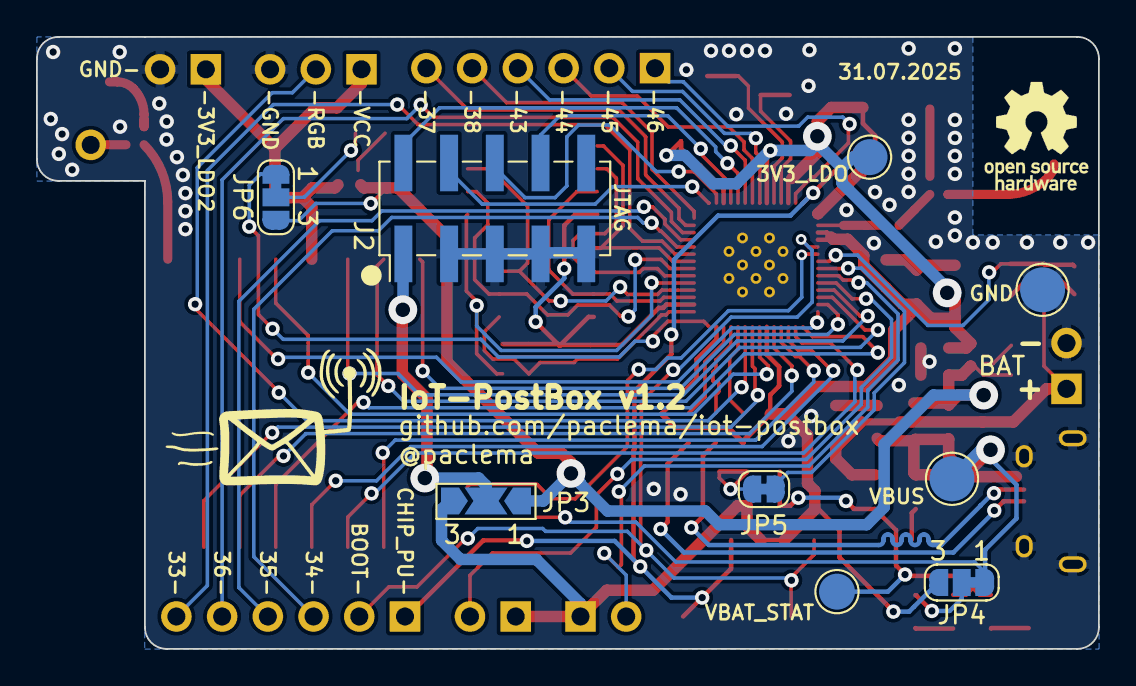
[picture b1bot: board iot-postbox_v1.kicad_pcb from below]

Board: 2 copper layers, 59.0 x 34.0 mm, 87 parts (11 on the bottom side), 72 nets.
